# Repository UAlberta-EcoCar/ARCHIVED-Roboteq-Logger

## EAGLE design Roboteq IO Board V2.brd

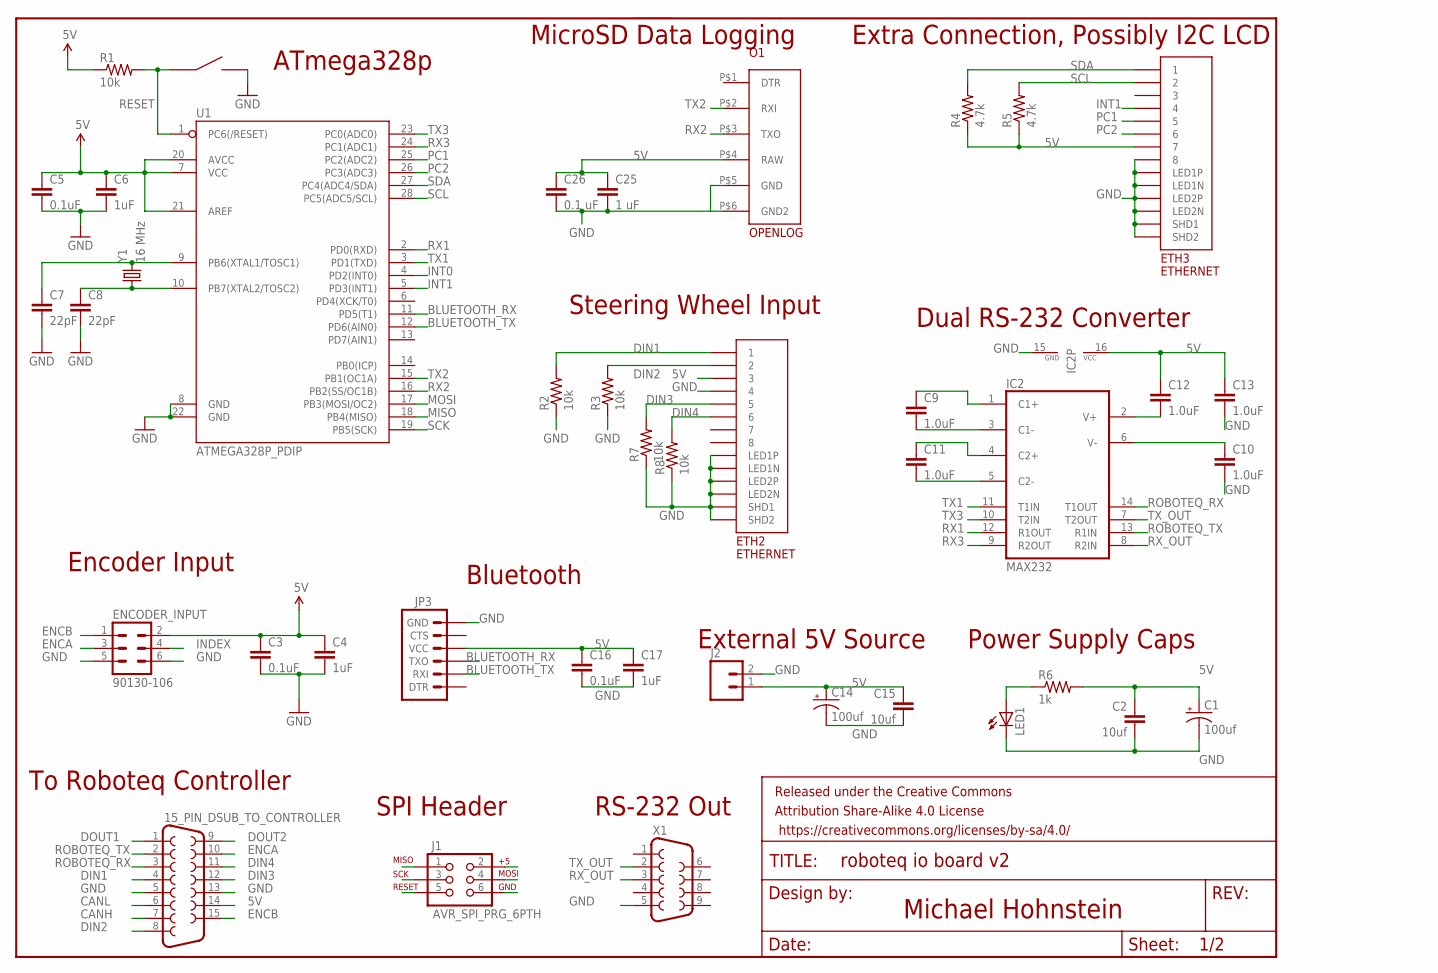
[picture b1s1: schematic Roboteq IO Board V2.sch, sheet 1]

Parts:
15_PIN_DSUB_TO_CONTROLLER: F15HP
C1, C14: 100uf; PANASONIC_C
C2, C15: 10uf; 0805
C3, C5, C16: 0.1uF; 0805
C4, C6, C17: 1uF; 0805
C7, C8: 22pF; 0805
C9, C10, C11, C12, C13: 1.0uF; 0805
C25: 1 uF; 0805
C26: 0.1 uF; 0805
ENCODER_INPUT: 90130-106; 90130-1?06
ETH2, ETH3: ETHERNET; A122645-ND
FRAME2: FRAME-LETTER; CREATIVE_COMMONS
IC2: MAX232; DIL16
J1: AVR_SPI_PRG_6PTH; 2X3
J2: M02PTH; 1X02
JP3: ARDUINO_SERIAL_PROGRAMPTH; 1X06
LED1: LEDCHIP-LED0805; CHIP-LED0805
O1: OPENLOG
R1, R2, R3, R7, R8: 10k; 0805
R4, R5: 4.7k; 0805
R6: 1k; 0805
U1: ATMEGA328P_PDIP; DIL28-3
U$3: EG4621CT-ND
X1: F09HP
Y1: 16 MHz; HC49US

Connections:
5V: 15_PIN_DSUB_TO_CONTROLLER.14, C1.+, C2.1, C3.1, C4.1, C5.1, C6.1, C12.1, C13.1, C14.+, C15.1, C16.1, C17.1, C25.1, C26.1, ENCODER_INPUT.2, ETH2.P$3 (3), ETH3.P$7 (7), IC2.16 (VCC), J1.2, J2.1, JP3.4 (VCC), O1.P$4 (RAW), R1.1, R4.1, R5.1, R6.2, U1.7 (VCC), U1.20 (AVCC), U1.21 (AREF); also elsewhere on the board
BLUETOOTH_RX: JP3.3 (TXO), U1.11 (PD5(T1))
BLUETOOTH_TX: JP3.2 (RXI), U1.12 (PD6(AIN0))
CANH: 15_PIN_DSUB_TO_CONTROLLER.7
CANL: 15_PIN_DSUB_TO_CONTROLLER.6
DIN1: 15_PIN_DSUB_TO_CONTROLLER.4, ETH2.P$1 (1), R2.2
DIN2: 15_PIN_DSUB_TO_CONTROLLER.8, ETH2.P$2 (2), R3.2
DIN3: 15_PIN_DSUB_TO_CONTROLLER.12, ETH2.P$5 (5), R7.2
DIN4: 15_PIN_DSUB_TO_CONTROLLER.11, ETH2.P$6 (6), R8.2
DOUT1: 15_PIN_DSUB_TO_CONTROLLER.1
DOUT2: 15_PIN_DSUB_TO_CONTROLLER.9
ENCA: 15_PIN_DSUB_TO_CONTROLLER.10, ENCODER_INPUT.3
ENCB: 15_PIN_DSUB_TO_CONTROLLER.15, ENCODER_INPUT.1
GND: 15_PIN_DSUB_TO_CONTROLLER.5, 15_PIN_DSUB_TO_CONTROLLER.13, C1.-, C2.2, C3.2, C4.2, C5.2, C6.2, C7.2, C8.2, C10.2, C13.2, C14.-, C15.2, C16.2, C17.2, C25.2, C26.2, ENCODER_INPUT.5, ENCODER_INPUT.6, ETH2.P$4 (4), ETH2.P$9 (LED1N), ETH2.P$10 (LED1P), ETH2.P$11 (LED2N), ETH2.P$12 (LED2P), ETH2.P$13 (SHD1), ETH2.P$14 (SHD2), ETH3.P$8 (8), ETH3.P$9 (LED1N), ETH3.P$10 (LED1P), ETH3.P$11 (LED2N), ETH3.P$12 (LED2P), ETH3.P$13 (SHD1), ETH3.P$14 (SHD2), IC2.15 (GND), J1.6, J2.2, JP3.6 (GND), LED1.C, O1.P$5 (GND), O1.P$6 (GND2), R2.1, R3.1, R7.1, R8.1, U1.8 (GND), U1.22 (GND), U$3.P$3, U$3.P$4, X1.5; also elsewhere on the board
INDEX: ENCODER_INPUT.4
INT0: U1.4 (PD2(INT0)); also elsewhere on the board
INT1: ETH3.P$4 (4), U1.5 (PD3(INT1))
MISO: J1.1, U1.18 (PB4(MISO))
MOSI: J1.4, U1.17 (PB3(MOSI/OC2))
unnamed: C7.1, U1.9 (PB6(XTAL1/TOSC1)), Y1.2
unnamed: C8.1, U1.10 (PB7(XTAL2/TOSC2)), Y1.1
unnamed: C9.1, IC2.1 (C1+)
unnamed: C9.2, IC2.3 (C1-)
unnamed: LED1.A, R6.1
unnamed: C10.1, IC2.6 (V-)
unnamed: C11.1, IC2.4 (C2+)
unnamed: C11.2, IC2.5 (C2-)
unnamed: C12.2, IC2.2 (V+)
PC1: ETH3.P$5 (5), U1.25 (PC2(ADC2))
PC2: ETH3.P$6 (6), U1.26 (PC3(ADC3))
RESET: J1.5, R1.2, U1.1 (PC6(/RESET)), U$3.P$1, U$3.P$2
ROBOTEQ_RX: 15_PIN_DSUB_TO_CONTROLLER.3, IC2.14 (T1OUT)
ROBOTEQ_TX: 15_PIN_DSUB_TO_CONTROLLER.2, IC2.13 (R1IN)
RX1: IC2.12 (R1OUT), U1.2 (PD0(RXD))
RX2: O1.P$3 (TXO), U1.16 (PB2(SS/OC1B))
RX3: IC2.9 (R2OUT), U1.24 (PC1(ADC1))
RX_OUT: IC2.8 (R2IN), X1.3
SCK: J1.3, U1.19 (PB5(SCK))
SCL: ETH3.P$2 (2), R5.2, U1.28 (PC5(ADC5/SCL))
SDA: ETH3.P$1 (1), R4.2, U1.27 (PC4(ADC4/SDA))
TX1: IC2.11 (T1IN), U1.3 (PD1(TXD))
TX2: O1.P$2 (RXI), U1.15 (PB1(OC1A))
TX3: IC2.10 (T2IN), U1.23 (PC0(ADC0))
TX_OUT: IC2.7 (T2OUT), X1.2

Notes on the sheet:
Dual RS-232 Converter
ATmega328p
Power Supply Caps
Michael Hohnstein
To Roboteq Controller
Encoder Input
RS-232 Out
SPI Header
Steering Wheel Input
MicroSD Data Logging
Extra Connection, Possibly I2C LCD
External 5V Source
Bluetooth

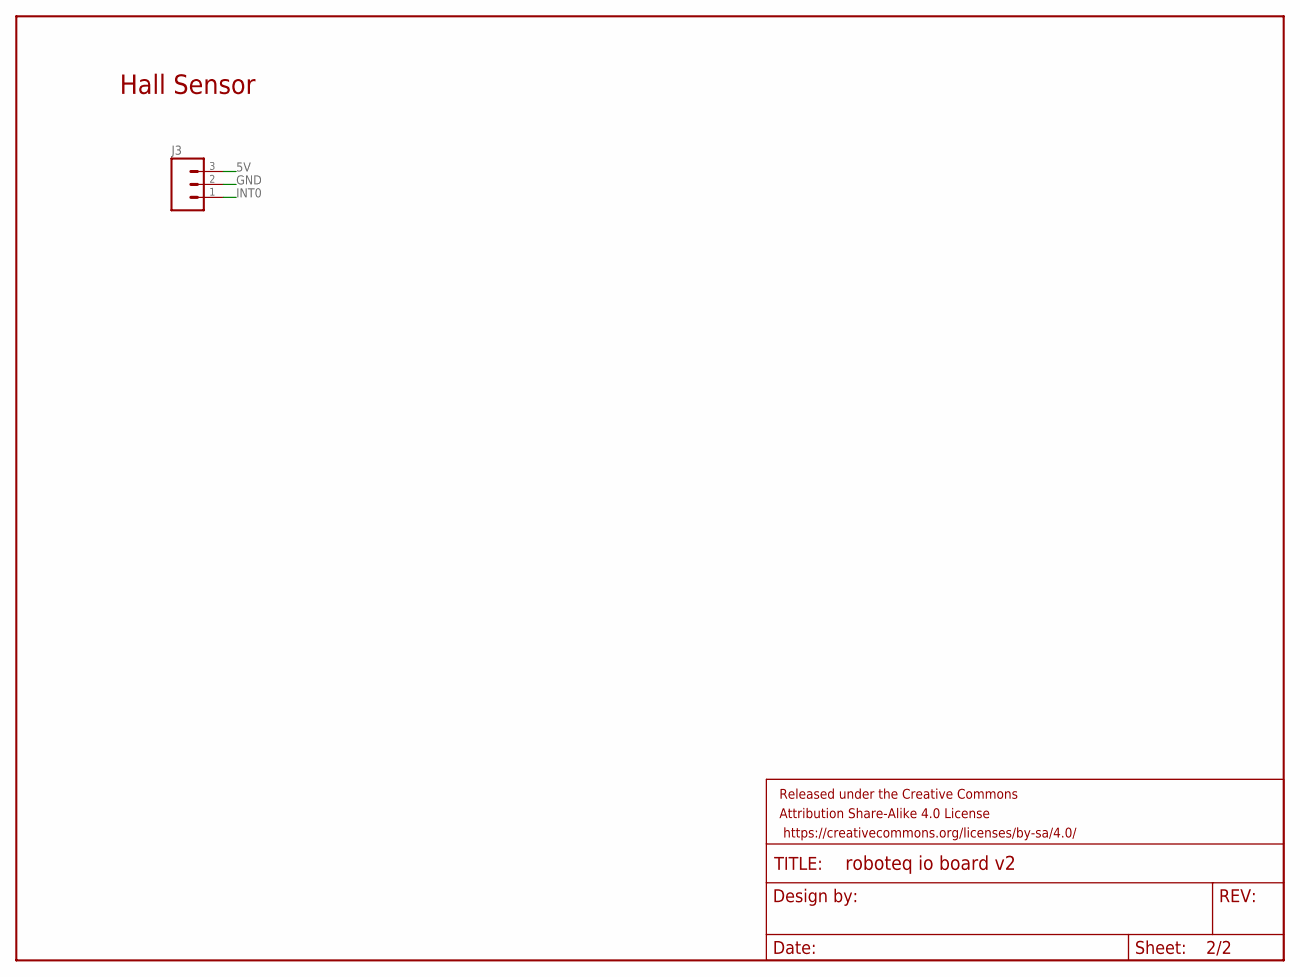
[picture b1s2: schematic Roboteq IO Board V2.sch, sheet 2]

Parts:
FRAME1: FRAME-LETTER; CREATIVE_COMMONS
J3: M03PTH; 1X03

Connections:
5V: J3.3; also elsewhere on the board
GND: J3.2; also elsewhere on the board
INT0: J3.1; also elsewhere on the board

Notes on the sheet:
Hall Sensor

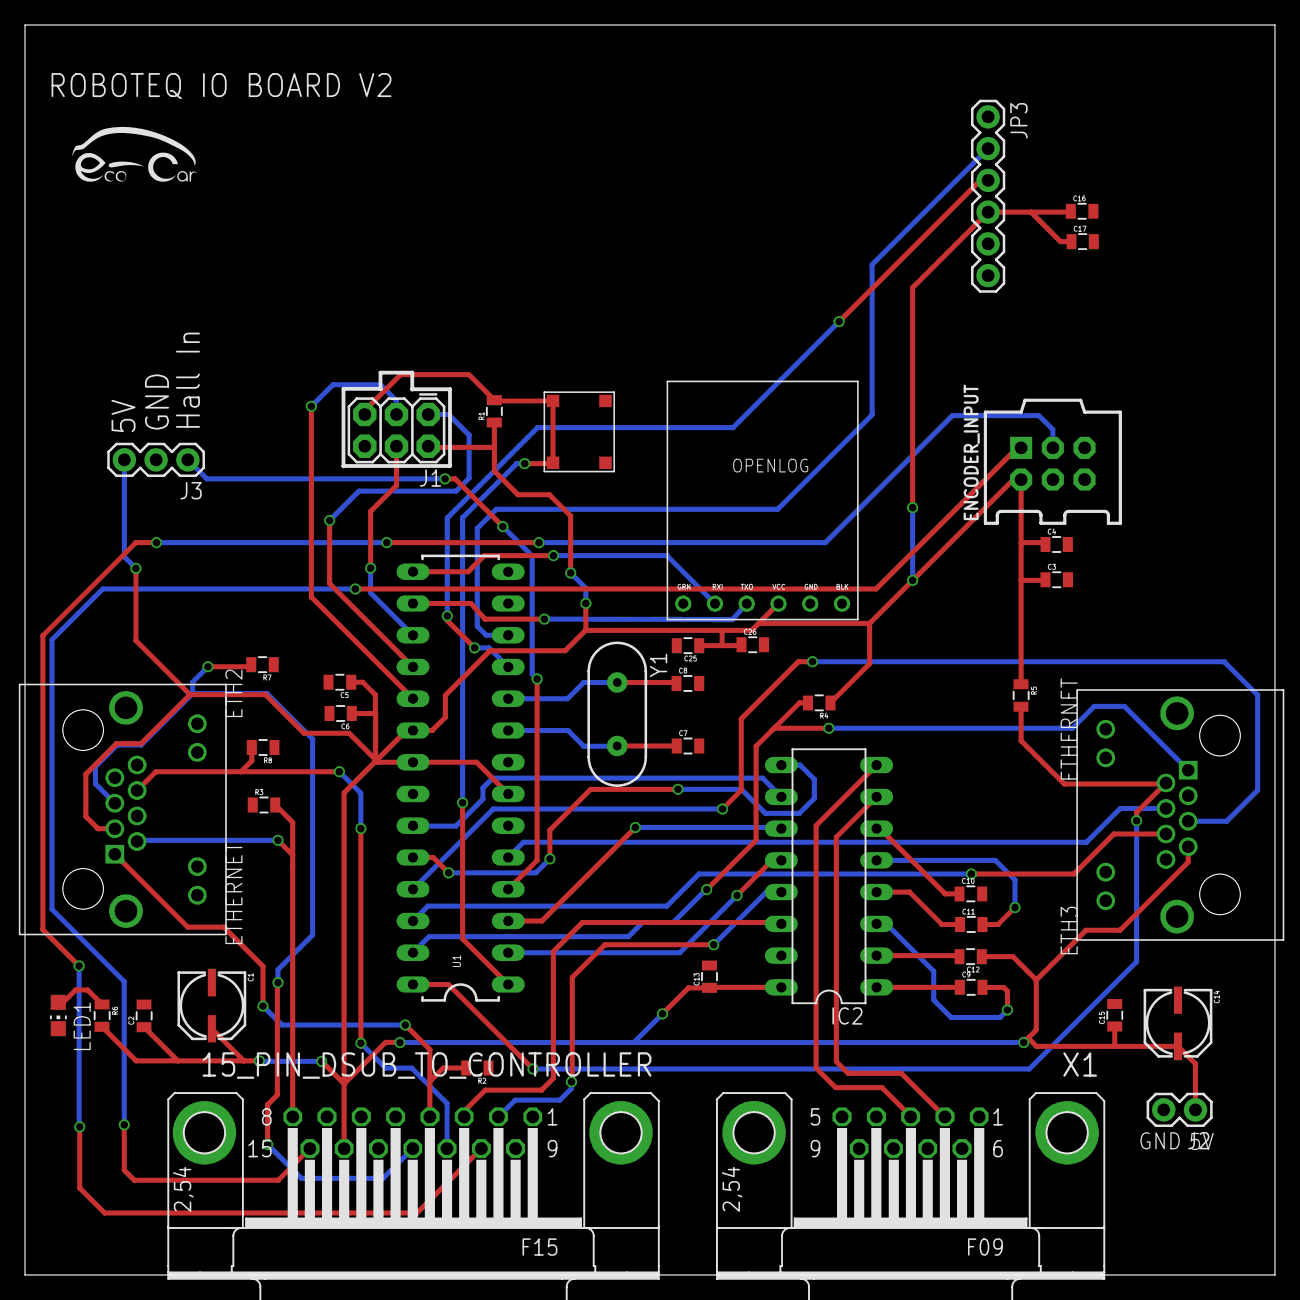
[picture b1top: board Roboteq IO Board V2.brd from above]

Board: 2 copper layers, 100.0 x 100.0 mm, 45 parts (0 on the bottom side), 39 nets.

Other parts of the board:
U$16: LOGO

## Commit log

2017-10-14 Uploaded Logger Board
2017-10-14 Git ignore

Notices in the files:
parts and their libraries:
SparkFun-Capacitors: Licensing: Creative Commons ShareAlike 4.0 International - https://creativecommons.org/licenses/by-sa/4.0
con-molex-c-grid: Copyright (C) 2009, Bob Starr
SparkFun-Aesthetics: Released under the Creative Commons Attribution Share-Alike 4.0 License
